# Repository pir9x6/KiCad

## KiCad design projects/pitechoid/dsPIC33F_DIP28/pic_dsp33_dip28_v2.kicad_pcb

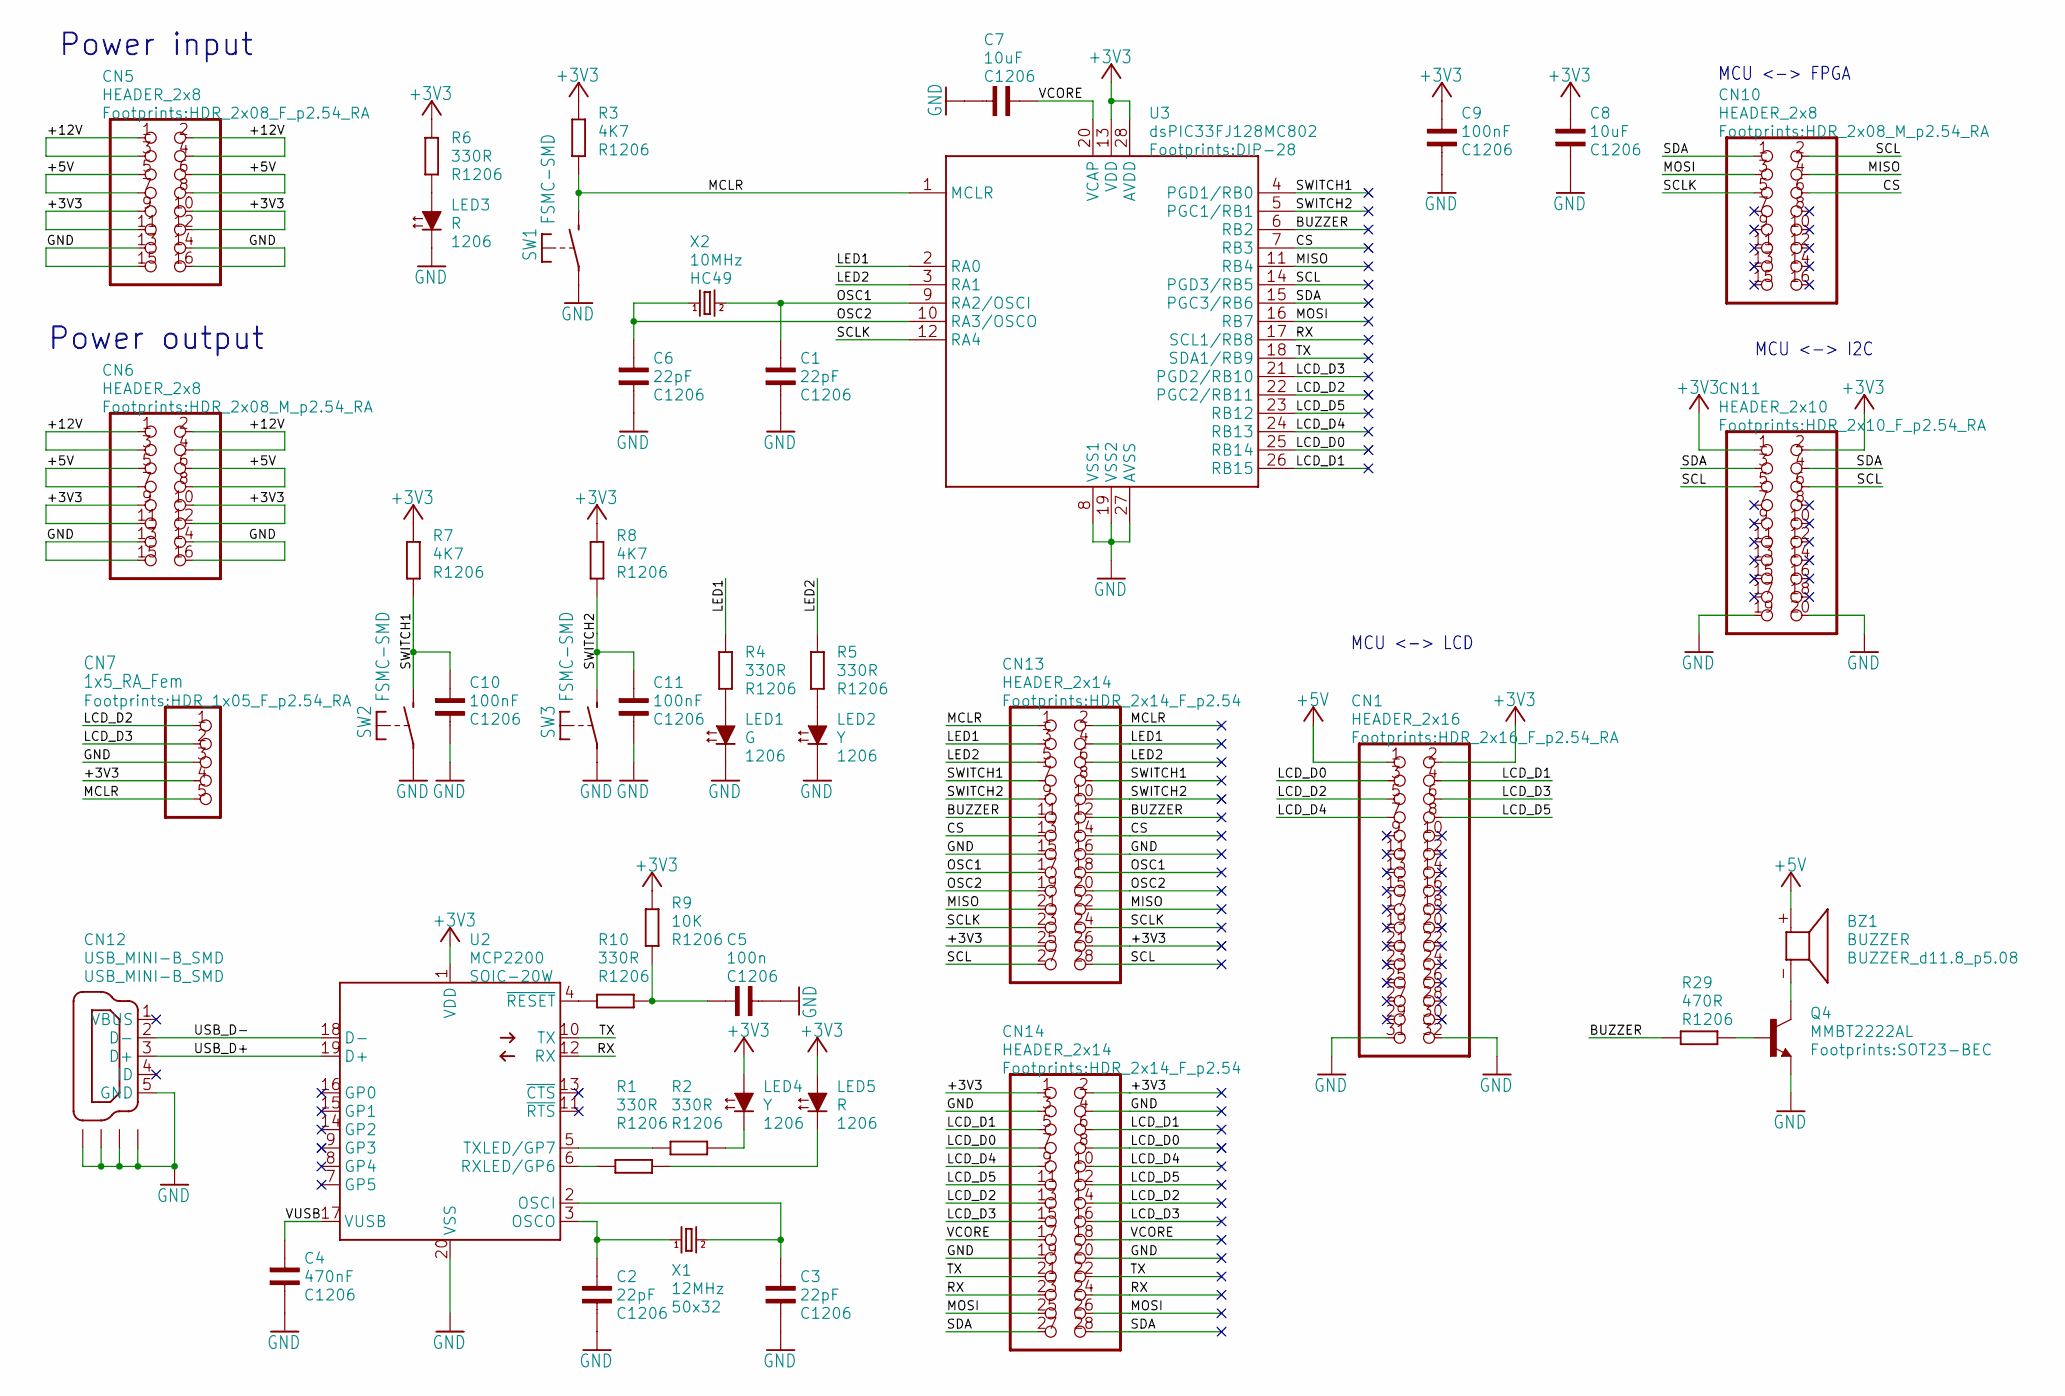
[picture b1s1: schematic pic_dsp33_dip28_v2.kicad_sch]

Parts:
BZ1: BUZZER; BUZZER_d12.0_p7.62
C1, C2, C3, C6: 22pF; C1206
C4: 470nF; C1206
C5: 100n; C1206
C7, C8: 10uF; C1206
C9, C10, C11: 100nF; C1206
CN1: HEADER_2x16; HDR_2x16_F_p2.54_RA
CN5: HEADER_2x8; HDR_2x08_F_p2.54_RA
CN6, CN10: HEADER_2x8; HDR_2x08_M_p2.54_RA
CN7: 1x5_RA_Fem; HDR_1x05_F_p2.54_RA
CN11: HEADER_2x10; HDR_2x10_F_p2.54_RA
CN12: USB_MINI-B_SMD
CN13, CN14: HEADER_2x14; HDR_2x14_F_p2.54
LED1: G; LED_3mm_GREEN
LED2: Y; LED_3mm_GREEN
LED3, LED5: R; LED_3mm_RED
LED4: Y; LED_3mm_YELLOW
Q4: MMBT2222AL; SOT23-BEC
R1, R2, R4, R5, R6, R10: 330R; R1206
R3, R7, R8: 4K7; R1206
R9: 10K; R1206
R29: 470R; R1206
SW1, SW2, SW3: FSMC-SMD; TACTILE_BUTTON_2P_SMD
U2: MCP2200; SOIC-20W
U3: dsPIC33FJ128MC802; DIP-28
X1: 12MHz; XTAL_SMD2_50x32
X2: 10MHz; XTAL_HC49_TH

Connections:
+3V3: C8.1, C9.1, CN1.2, CN5.9, CN5.10, CN5.11, CN5.12, CN6.9, CN6.10, CN6.11, CN6.12, CN7.4, CN11.1, CN11.2, CN13.25, CN13.26, CN14.1, CN14.2, LED4.A, LED5.A, R3.1, R6.1, R7.1, R8.1, R9.1, U2.1 (VDD), U3.13 (VDD), U3.28 (AVDD)
+5V: BZ1.+ (1), CN1.1, CN5.5, CN5.6, CN5.7, CN5.8, CN6.5, CN6.6, CN6.7, CN6.8
/pic_dsp33_dip28_v2_1/+12V: CN5.1, CN5.2, CN5.3, CN5.4, CN6.1, CN6.2, CN6.3, CN6.4
/pic_dsp33_dip28_v2_1/BUZZER: CN13.11, CN13.12, R29.1, U3.6 (RB2)
/pic_dsp33_dip28_v2_1/CS: CN10.6, CN13.13, CN13.14, U3.7 (RB3)
/pic_dsp33_dip28_v2_1/LCD_D0: CN1.3, CN14.7, CN14.8, U3.25 (RB14)
/pic_dsp33_dip28_v2_1/LCD_D1: CN1.4, CN14.5, CN14.6, U3.26 (RB15)
/pic_dsp33_dip28_v2_1/LCD_D2: CN1.5, CN7.1, CN14.13, CN14.14, U3.22 (PGC2/RB11)
/pic_dsp33_dip28_v2_1/LCD_D3: CN1.6, CN7.2, CN14.15, CN14.16, U3.21 (PGD2/RB10)
/pic_dsp33_dip28_v2_1/LCD_D4: CN1.7, CN14.9, CN14.10, U3.24 (RB13)
/pic_dsp33_dip28_v2_1/LCD_D5: CN1.8, CN14.11, CN14.12, U3.23 (RB12)
/pic_dsp33_dip28_v2_1/LED1: CN13.3, CN13.4, R4.1, U3.2 (RA0)
/pic_dsp33_dip28_v2_1/LED2: CN13.5, CN13.6, R5.1, U3.3 (RA1)
/pic_dsp33_dip28_v2_1/MCLR: CN7.5, CN13.1, CN13.2, R3.2, SW1.2 (S), U3.1 (MCLR)
/pic_dsp33_dip28_v2_1/MISO: CN10.4, CN13.21, CN13.22, U3.11 (RB4)
/pic_dsp33_dip28_v2_1/MOSI: CN10.3, CN14.25, CN14.26, U3.16 (RB7)
/pic_dsp33_dip28_v2_1/OSC1: C1.1, CN13.17, CN13.18, U3.9 (RA2/OSCI), X2.2
/pic_dsp33_dip28_v2_1/OSC2: C6.1, CN13.19, CN13.20, U3.10 (RA3/OSCO), X2.1
/pic_dsp33_dip28_v2_1/RX: CN14.23, CN14.24, U2.12 (RX), U3.17 (SCL1/RB8)
/pic_dsp33_dip28_v2_1/SCL: CN10.2, CN11.5, CN11.6, CN13.27, CN13.28, U3.14 (PGD3/RB5)
/pic_dsp33_dip28_v2_1/SCLK: CN10.5, CN13.23, CN13.24, U3.12 (RA4)
/pic_dsp33_dip28_v2_1/SDA: CN10.1, CN11.3, CN11.4, CN14.27, CN14.28, U3.15 (PGC3/RB6)
/pic_dsp33_dip28_v2_1/SWITCH1: C10.1, CN13.7, CN13.8, R7.2, SW2.2 (S), U3.4 (PGD1/RB0)
/pic_dsp33_dip28_v2_1/SWITCH2: C11.1, CN13.9, CN13.10, R8.2, SW3.2 (S), U3.5 (PGC1/RB1)
/pic_dsp33_dip28_v2_1/TX: CN14.21, CN14.22, U2.10 (TX), U3.18 (SDA1/RB9)
/pic_dsp33_dip28_v2_1/USB_D+: CN12.3 (D+), U2.19 (D+)
/pic_dsp33_dip28_v2_1/USB_D-: CN12.2 (D-), U2.18 (D-)
/pic_dsp33_dip28_v2_1/VCORE: C7.1, CN14.17, CN14.18, U3.20 (VCAP)
/pic_dsp33_dip28_v2_1/VUSB: C4.1, U2.17 (VUSB)
GND: C1.2, C2.2, C3.2, C4.2, C5.2, C6.2, C7.2, C8.2, C9.2, C10.2, C11.2, CN1.31, CN1.32, CN5.13, CN5.14, CN5.15, CN5.16, CN6.13, CN6.14, CN6.15, CN6.16, CN7.3, CN11.19, CN11.20, CN12.5 (GND), CN12.H1, CN12.H2, CN12.H3, CN12.H4, CN13.15, CN13.16, CN14.3, CN14.4, CN14.19, CN14.20, LED1.K, LED2.K, LED3.K, Q4.E, SW1.1, SW2.1, SW3.1, U2.20 (VSS), U3.8 (VSS1), U3.19 (VSS2), U3.27 (AVSS)
unnamed: BZ1.- (2), Q4.C
unnamed: C5.1, R9.2, R10.1
unnamed: LED1.A, R4.2
unnamed: LED2.A, R5.2
unnamed: LED3.A, R6.2
unnamed: LED4.K, R2.1
unnamed: LED5.K, R1.1
unnamed: Q4.B, R29.2
unnamed: C3.1, U2.2 (OSCI), X1.2
unnamed: C2.1, U2.3 (OSCO), X1.1
unnamed: R1.2, U2.6 (RXLED/GP6)
unnamed: R2.2, U2.5 (TXLED/GP7)
unnamed: R10.2, U2.4 (~RESET)

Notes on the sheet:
MCU <-> LCD
MCU <-> I2C
Power input
Power output
MCU <-> FPGA

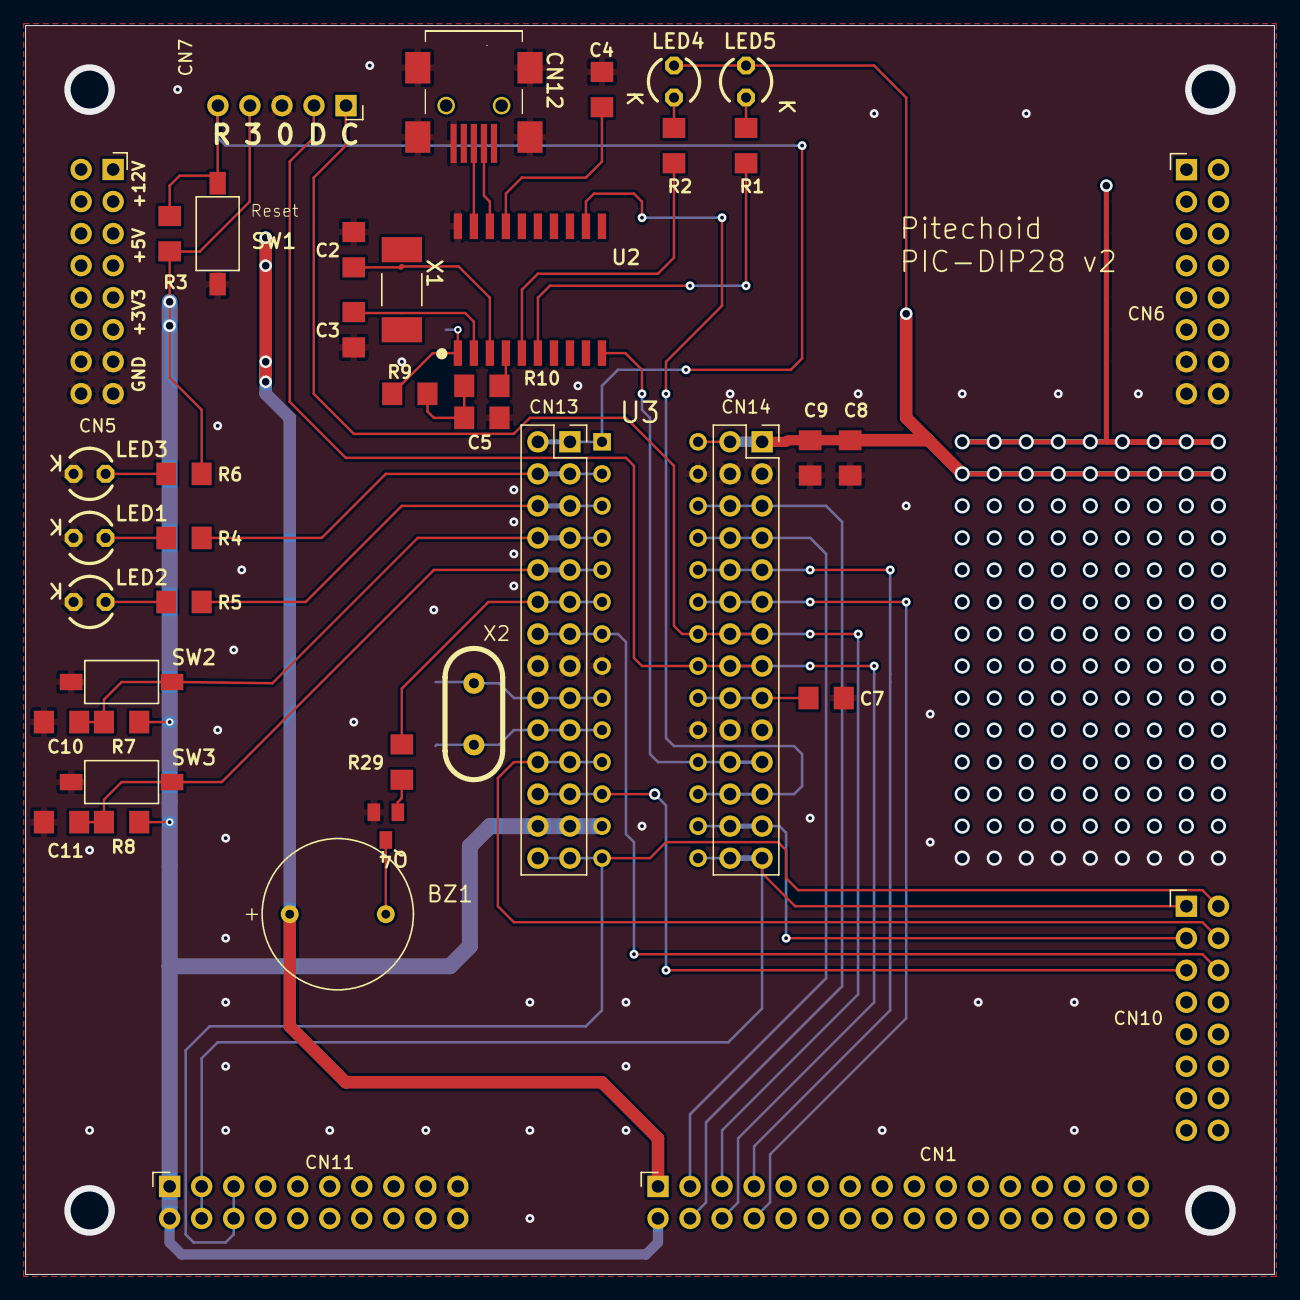
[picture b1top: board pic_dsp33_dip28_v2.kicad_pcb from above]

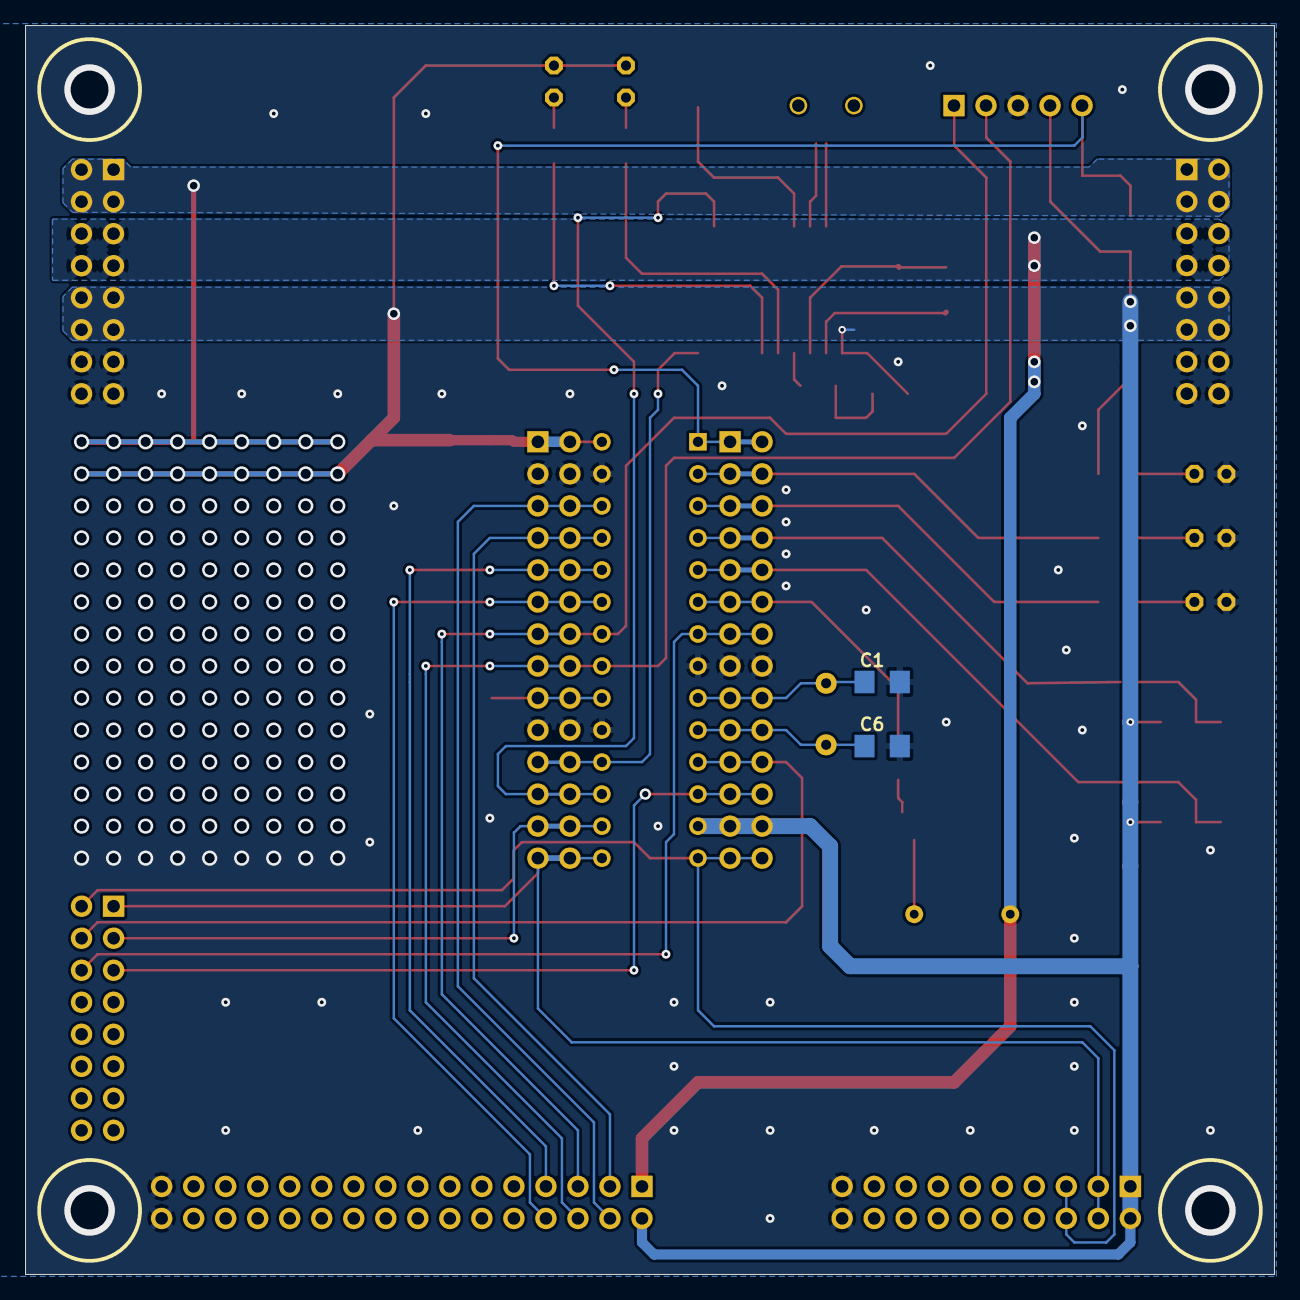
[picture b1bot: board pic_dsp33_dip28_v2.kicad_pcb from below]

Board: 2 copper layers, 99.1 x 99.1 mm, 45 parts (2 on the bottom side), 43 nets.

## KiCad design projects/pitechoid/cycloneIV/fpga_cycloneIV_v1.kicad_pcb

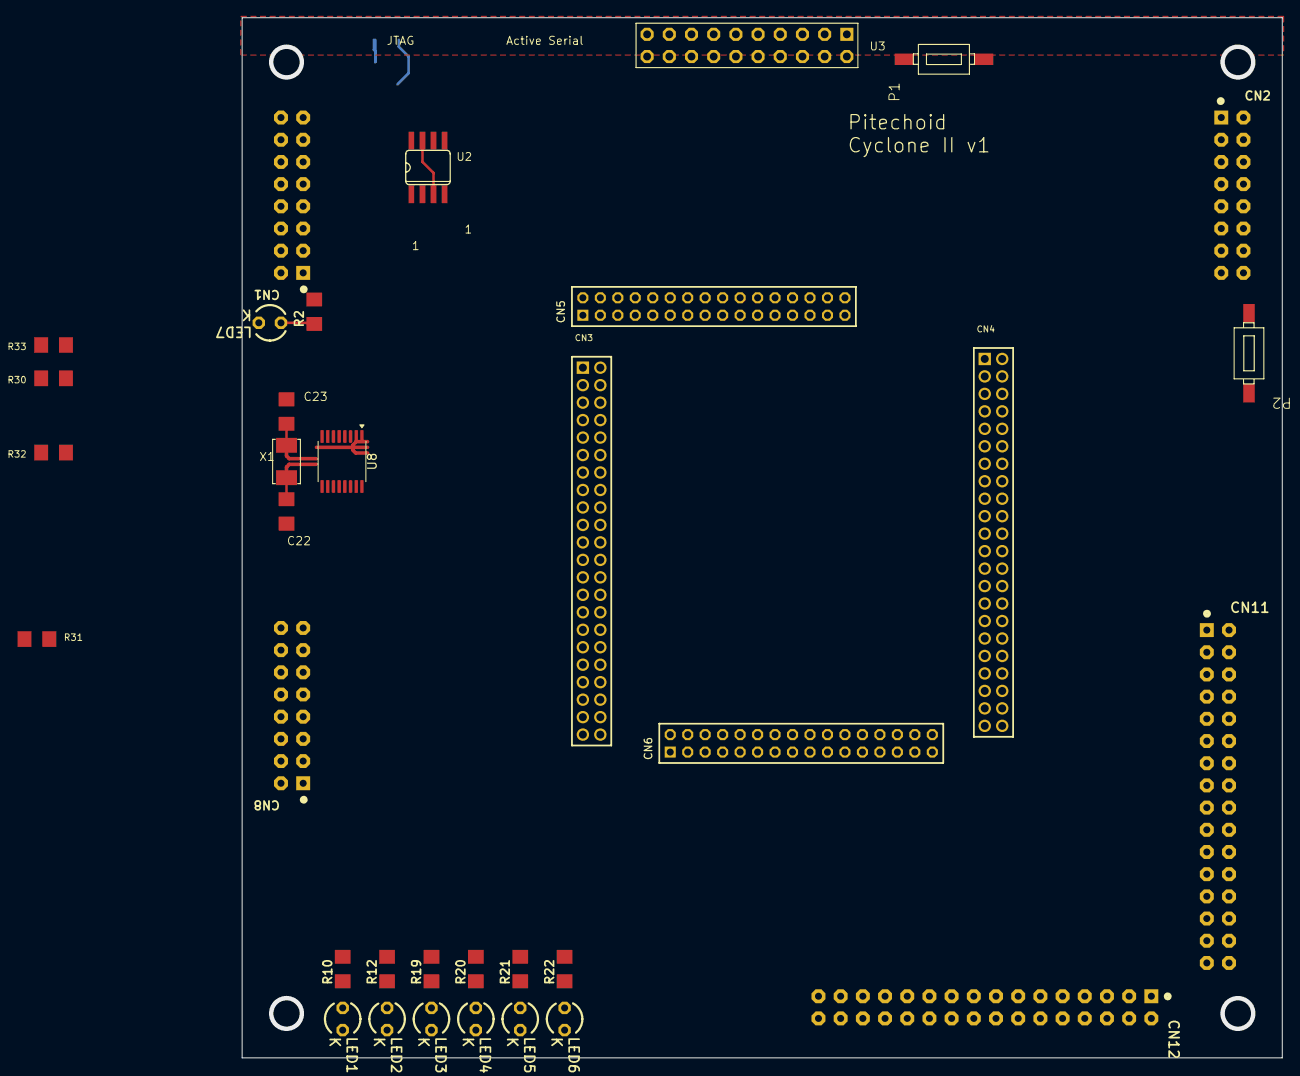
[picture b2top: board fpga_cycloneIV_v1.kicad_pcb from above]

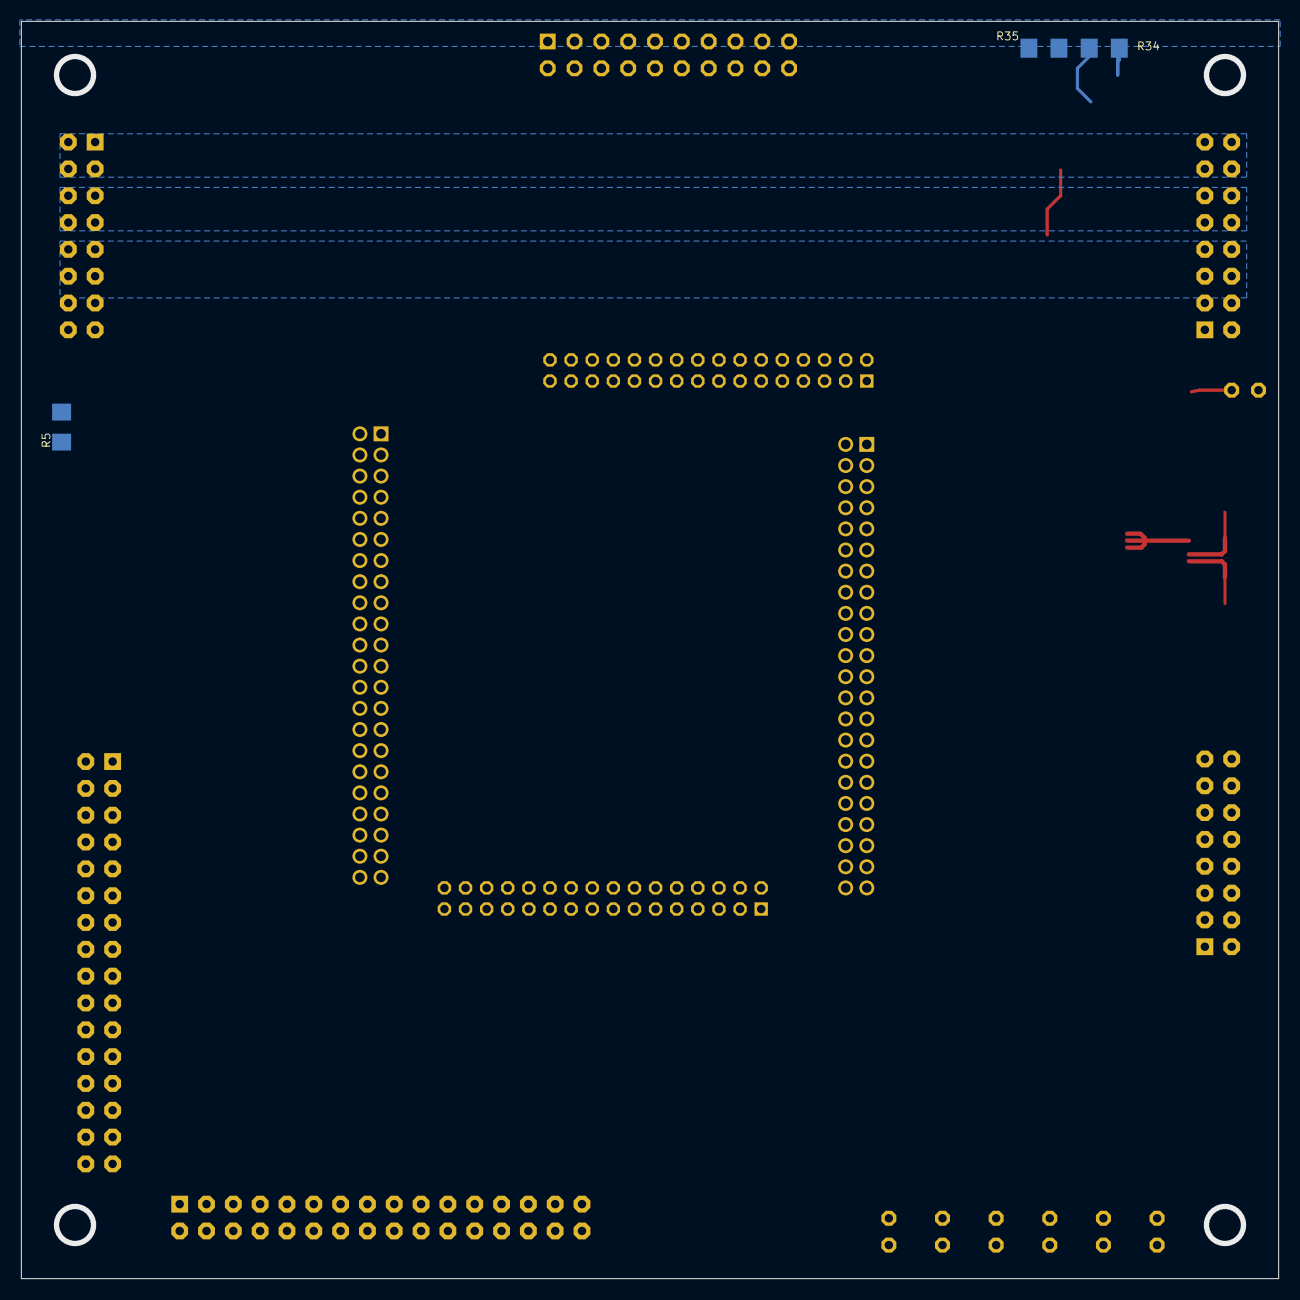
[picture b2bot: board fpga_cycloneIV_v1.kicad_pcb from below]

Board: 2 copper layers, 119.1 x 119.1 mm, 38 parts (3 on the bottom side), 15 nets.

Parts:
C22, C23: 22p; C1206
CN1, CN2, CN8: HEADER_2x8; HEADER_2x8_M_p2.54_TH_RA
CN3, CN4: HDR_2x22; 2X22_2MM
CN5, CN6: HEADER_2X16_2.00; 2X16_2MM
CN11, CN12: HEADER_2x16; HEADER_2x16_M_p2.54_TH_RA
LED1, LED2, LED3, LED4, LED5, LED6: LED; LED_3mm_GREEN
LED7: LED; LED_3mm_RED
P1, P2: FSMC-SMD
R2, R10, R12, R19, R20, R21, R22: 330R; R1206
R5, R30, R31, R32, R33, R34, R35: xxK; R1206
U2: EPCS4; SOIC08
U3: CAMERA_OV5642
U8: CY22393FXC; TSSOP-16_4.4x5mm_p0.65mm
X1: 27M; SMD2_50X32

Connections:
+3V3: CN1.5, CN1.6, CN1.7, CN1.8, CN2.9, CN2.10, CN2.11, CN2.12, CN12.32, R2.2, U2.3 (VCC@1), U2.7 (VCC@2), U2.8 (VCC@3), U3.1 (VCC), U8.2 (VDD), U8.14 (AVDD), U8.15 (S2), U8.16 (~SHUTDWN)
/fpga_cycloneIV_v1_1/+5V: CN1.9, CN1.10, CN1.11, CN1.12, CN2.5, CN2.6, CN2.7, CN2.8
/fpga_cycloneIV_v1_1/+12V: CN1.13, CN1.14, CN1.15, CN1.16, CN2.1, CN2.2, CN2.3, CN2.4
/fpga_cycloneIV_v1_2/OSCI: C23.2, U8.4 (XIN), X1.1
/fpga_cycloneIV_v1_2/OSCO: C22.2, U8.5 (XOUT), X1.2
/fpga_cycloneIV_v1_2/SCL: CN8.16, CN11.2, U3.3 (SCL), U8.13 (SCL)
/fpga_cycloneIV_v1_2/SDA: CN8.15, CN11.1, U3.4 (SDA), U8.12 (SDA)
GND: C22.1, C23.1, CN1.1, CN1.2, CN1.3, CN1.4, CN2.13, CN2.14, CN2.15, CN2.16, CN11.31, CN11.32, CN12.1, CN12.2, LED1.K, LED2.K, LED3.K, LED4.K, LED5.K, LED6.K, LED7.K, P1.P$1, P2.P$1 (P_P$1), U2.4 (GND), U3.2 (GND), U8.3 (AVSS), U8.11 (VSS)
unnamed: LED1.A, R10.1
unnamed: LED2.A, R12.1
unnamed: LED3.A, R19.1
unnamed: LED4.A, R20.1
unnamed: LED5.A, R21.1
unnamed: LED6.A, R22.1
unnamed: LED7.A, R2.1

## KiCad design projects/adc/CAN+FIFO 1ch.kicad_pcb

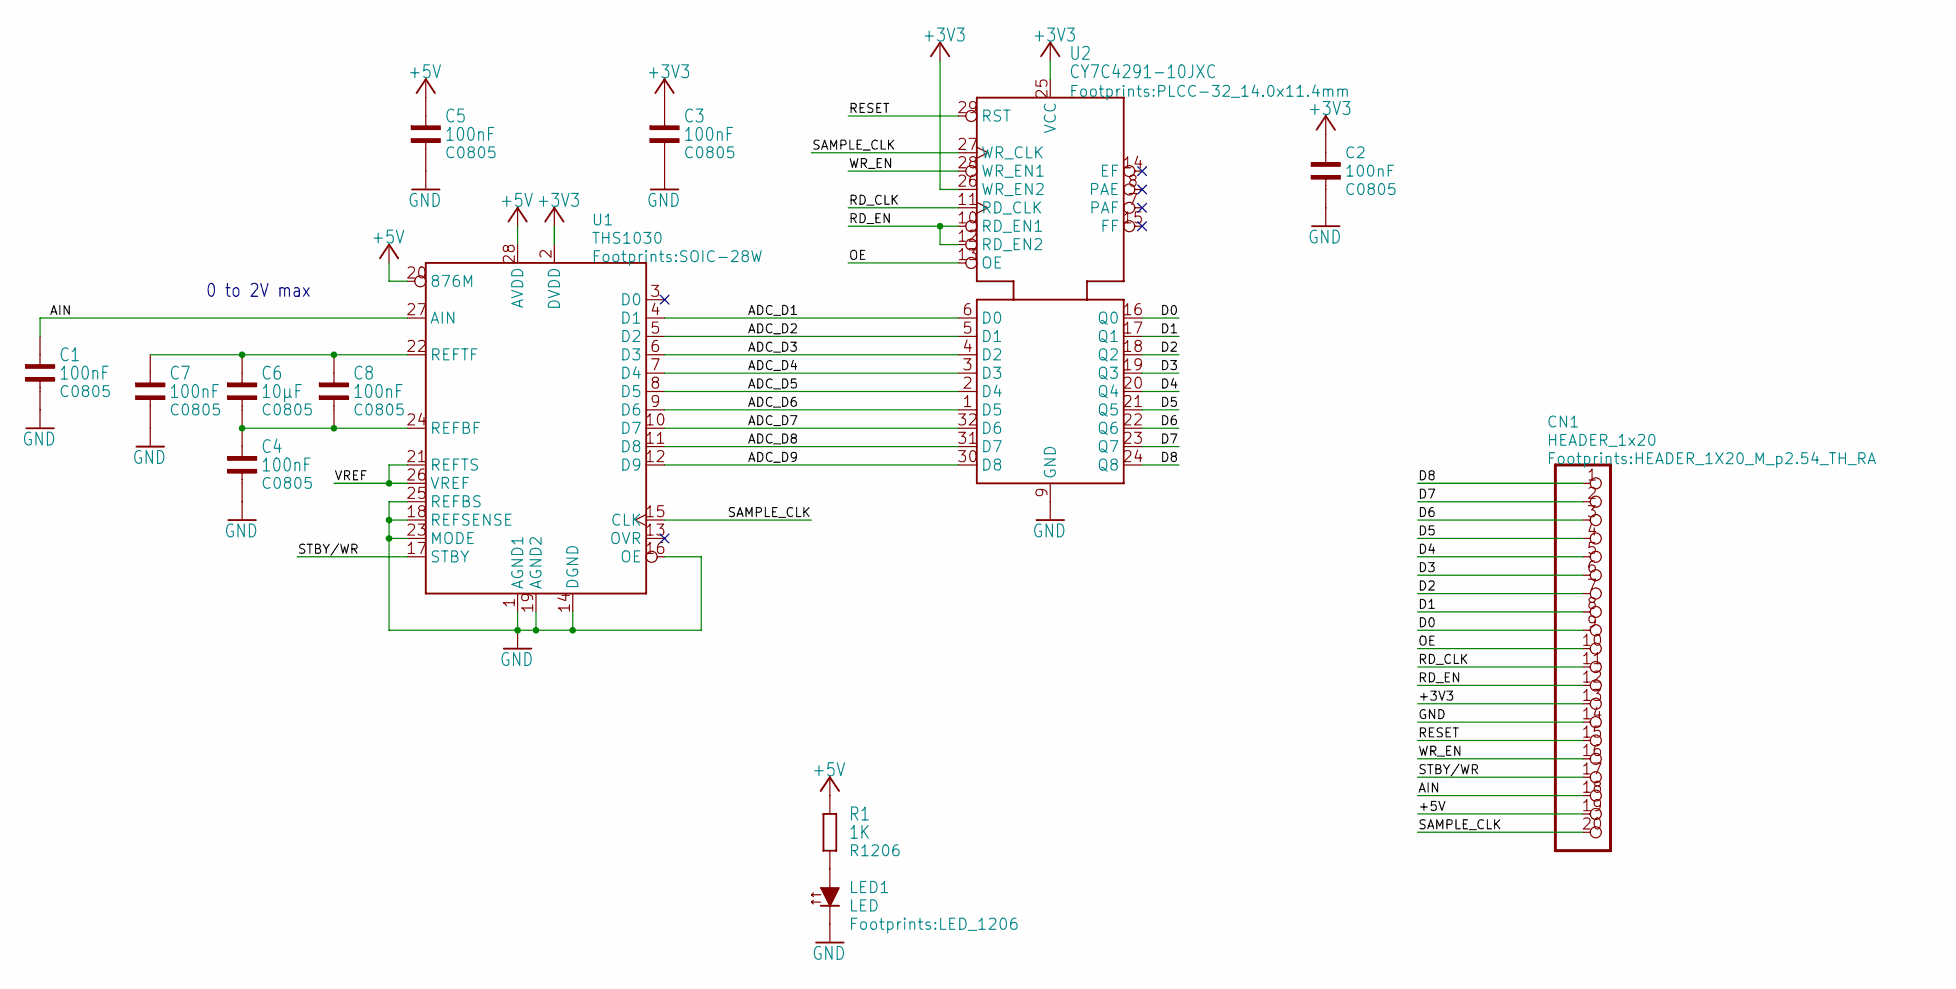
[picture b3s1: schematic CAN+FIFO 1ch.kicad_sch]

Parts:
C1, C2, C3, C4, C5, C7, C8: 100nF; C0805
C6: 10µF; C0805
CN1: HEADER_1x20; HEADER_1X20_M_p2.54_TH_RA
LED1: LED; LED_1206
R1: 1K; R1206
U1: THS1030; SOIC-28W
U2: CY7C4291-10JXC; PLCC-32_14.0x11.4mm

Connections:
+3V3: C2.1, C3.1, CN1.13, U1.2 (DVDD), U2.25 (VCC), U2.26 (WR_EN2)
+5V: C5.1, CN1.19, R1.2, U1.20 (876M), U1.28 (AVDD)
/ADC_D1: U1.4 (D1), U2.6 (D0)
/ADC_D2: U1.5 (D2), U2.5 (D1)
/ADC_D3: U1.6 (D3), U2.4 (D2)
/ADC_D4: U1.7 (D4), U2.3 (D3)
/ADC_D5: U1.8 (D5), U2.2 (D4)
/ADC_D6: U1.9 (D6), U2.1 (D5)
/ADC_D7: U1.10 (D7), U2.32 (D6)
/ADC_D8: U1.11 (D8), U2.31 (D7)
/ADC_D9: U1.12 (D9), U2.30 (D8)
/AIN: C1.1, CN1.18, U1.27 (AIN)
/D0: CN1.9, U2.16 (Q0)
/D1: CN1.8, U2.17 (Q1)
/D2: CN1.7, U2.18 (Q2)
/D3: CN1.6, U2.19 (Q3)
/D4: CN1.5, U2.20 (Q4)
/D5: CN1.4, U2.21 (Q5)
/D6: CN1.3, U2.22 (Q6)
/D7: CN1.2, U2.23 (Q7)
/D8: CN1.1, U2.24 (Q8)
/OE: CN1.10, U2.13 (OE)
/RD_CLK: CN1.11, U2.11 (RD_CLK)
/RD_EN: CN1.12, U2.10 (RD_EN1), U2.12 (RD_EN2)
/RESET: CN1.15, U2.29 (RST)
/SAMPLE_CLK: CN1.20, U1.15 (CLK), U2.27 (WR_CLK)
/STBY/WR: CN1.17, U1.17 (STBY)
/VREF: U1.21 (REFTS), U1.26 (VREF)
/WR_EN: CN1.16, U2.28 (WR_EN1)
GND: C1.2, C2.2, C3.2, C4.2, C5.2, C7.2, CN1.14, LED1.K, U1.1 (AGND1), U1.14 (DGND), U1.16 (OE), U1.18 (REFSENSE), U1.19 (AGND2), U1.23 (MODE), U1.25 (REFBS), U2.9 (GND)
unnamed: LED1.A, R1.1
unnamed: C4.1, C6.2, C8.2, U1.24 (REFBF)
unnamed: C6.1, C7.1, C8.1, U1.22 (REFTF)

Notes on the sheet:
0 to 2V max

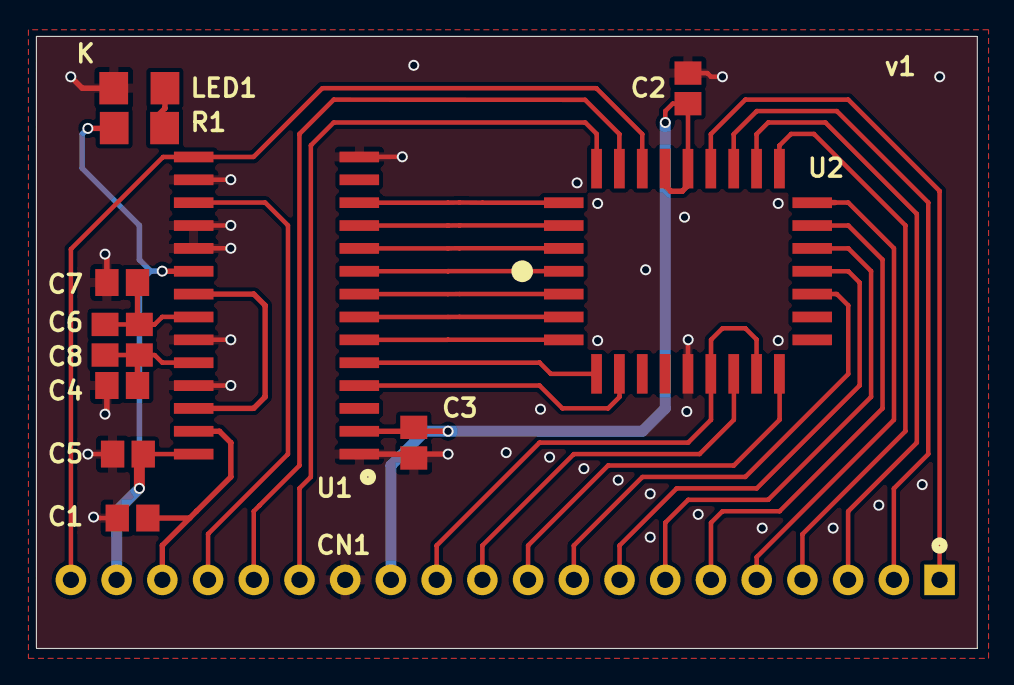
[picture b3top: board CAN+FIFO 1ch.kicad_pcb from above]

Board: 2 copper layers, 52.3 x 34.0 mm, 13 parts (0 on the bottom side), 33 nets.
